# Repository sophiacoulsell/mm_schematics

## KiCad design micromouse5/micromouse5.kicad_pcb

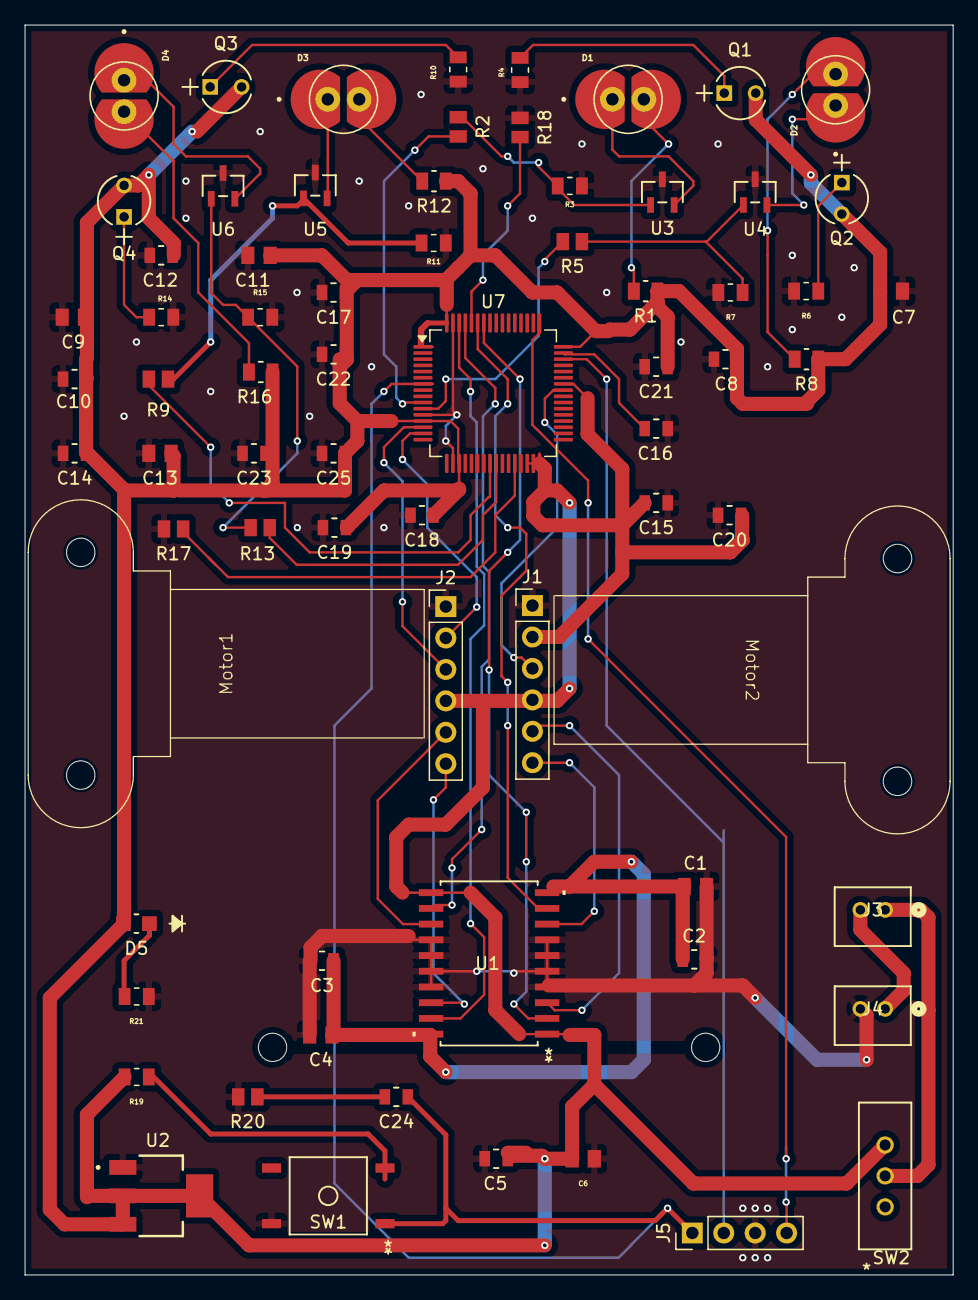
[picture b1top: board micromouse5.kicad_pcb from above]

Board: 2 copper layers, 75.0 x 101.0 mm, 71 parts (0 on the bottom side), 45 nets.

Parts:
C1, C4, C7, C9, C11, C13: 4.7 uF; CAP_GRM0805_2X1P25_MUR
C2: 10 uF; G-21_MUR(0.1)
C3: 0.1 uF; G-21_MUR(10)
C5: 10 uF; G-21_MUR(10)
C6: 22 uF; CAPC2012X140N
C8, C10, C12, C14: 0.1uF; G-21_MUR(0.1)
C15, C16: 2.2 uF; G-21_MUR
C17, C18, C19, C20, C21, C22, C23, C24: 0.1 uF; G-21_MUR(0.1)
C25: 1 uF; G-21_MUR (1uF)
D1, D2, D3, D4: IR Emitter; DIO_SFH_4545 (IR- Emitter)
D5: LED; LED_LTST-C170GKT_LTO
J1, J2: Conn_01x06_Pin; PinHeader_1x06_P2.54mm_Vertical
J3: JST 2; CONN2_B2B-PH-K-S_JST
J4: JST 1; CONN2_B2B-PH-K-S_JST
J5: Conn_01x04_Pin; PinHeader_1x04_P2.54mm_Vertical
Motor1, Motor2: Pololu_Motor
Q1, Q2, Q3, Q4: IR Receiver; NoneP157X157-2_LTO (IR- Receiver)
R1, R8, R12, R16: 51 Ohm; BO_CR0805(51 ohm)
R2, R5, R9, R13, R20: 100 Ohm; STA_RNCP0805_STP(100 ohm)
R3, R7, R11, R15: 47 kOhm; RESC2012X60N (47kΩ)
R4, R6, R10, R14: 1.8kOhm; RESC2012X60N (1.8kΩ)
R17, R18: 10 kOhm; STA_RNCP0805_STP
R19: 47k Ohm; RESC2012X60N (47kΩ)
R21: 300 Ohm; RESC2012X60N
SW1: Button; SW4_FSM4JSMA_TEC
SW2: EG1218; SW_1218_EWI
U1: HBridge; SO-20_STM
U2: Voltage Regulator; SOT230P700X185-4N
U3, U4, U5, U6: MOSFET; SOT-23_3L_ONS (mosfet)
U7: STM32F205RGTx; LQFP-64_10x10mm_P0.5mm

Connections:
3V3: C5.1, C6.1, C7.2, C8.2, C9.2, C10.2, C11.2, C12.2, C13.2, C14.2, C15.2, C17.2, C18.2, C19.2, C20.2, C21.2, C22.2, C23.1, C25.1, D5.2 (A), J1.2, J1.4, J2.4, Q1.2, Q2.2, Q3.2, Q4.2, R1.2, R8.2, R12.2, R16.2, R19.1, SW2.1, U1.1 (ENABLE_1), U1.11 (ENABLE_2), U2.2 (OUTPUT), U2.3 (INPUT), U2.4 (VOUT), U7.1 (VBAT), U7.13 (VDDA), U7.19 (VDD), U7.30 (PB11), U7.31 (VCAP_1), U7.32 (VDD), U7.42 (PA9), U7.48 (VDD), U7.64 (VDD)
GND: C1.1, C2.2, C3.1, C4.2, C5.2, C6.2, C7.1, C8.1, C9.1, C10.1, C11.1, C12.1, C13.1, C14.1, C15.1, C16.1, C17.1, C18.1, C19.1, C20.1, C21.1, C22.1, C23.2, C25.2, J1.1, J2.1, J4.2, J5.3, R3.1, R4.1, R6.1, R7.1, R10.1, R11.1, R14.1, R15.1, R17.2, R18.1, R20.2, R21.2, SW1.4, U1.4 (GND), U1.5 (GND), U1.6 (GND), U1.7 (GND), U1.14 (GND), U1.15 (GND), U1.16 (GND), U1.17 (GND), U2.1 (GND), U3.3, U4.3, U5.3, U6.3, U7.12 (VSSA), U7.18 (VSS), U7.63 (VSS)
ML1: J1.6, U1.8 (OUTPUT_2)
ML2: J1.5, U1.3 (OUTPUT_1)
MR1: J2.6, U1.18 (OUTPUT_4)
MR2: J2.5, U1.13 (OUTPUT_3)
NRST: C24.1, J5.1, SW1.1, U7.7 (NRST)
unnamed: C24.2, R20.1
unnamed: D1.A, R1.1
unnamed: D1.C, U3.2
unnamed: D2.A, R8.1
unnamed: D2.C, U4.2
unnamed: D3.A, R12.1
unnamed: D3.C, U5.2
unnamed: D4.A, R16.1
unnamed: D4.C, U6.2
unnamed: D5.1 (K), R21.1
unnamed: J3.1, SW2.2
unnamed: J3.2, J4.1
unnamed: Q1.1, R4.2
unnamed: Q2.1, R6.2
unnamed: Q3.1, R10.2
unnamed: Q4.1, R14.2
unnamed: R2.2, R3.2, U3.1
unnamed: R5.2, R7.2, U4.1
unnamed: R9.2, R11.2, U5.1
unnamed: R13.2, R15.2, U6.1
unnamed: R19.2, SW1.2
unnamed: R18.2, U7.60 (BOOT0)
unnamed: R17.1, U7.28 (PB2)
unnamed: C16.2, U7.47 (VCAP_2)
PA0: J2.3, U7.14 (PA0)
PA1: J2.2, U7.15 (PA1)
PA8: J1.3, U7.41 (PA8)
PB6: U1.2 (INPUT_1), U7.58 (PB6)
PB7: U1.9 (INPUT_2), U7.59 (PB7)
PB8: U1.12 (INPUT_3), U7.61 (PB8)
PB9: U1.19 (INPUT_4), U7.62 (PB9)
PC2: R2.1, U7.10 (PC2)
PC3: R5.1, U7.11 (PC3)
PC4: R9.1, U7.24 (PC4)
PC5: R13.1, U7.25 (PC5)
SWCLK: J5.4, U7.49 (PA14)
SWDIO: J5.2, U7.46 (PA13)
VCC: C1.2, C2.1, C3.2, C4.1, U1.10 (VS), U1.20 (VSS)

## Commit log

2025-02-21 added initial project
2025-02-21 added h-bridge
2025-02-21 added voltage regulator
2025-02-26 Schematic MM
    Assignment 5
2025-02-26 Trying to commit footprints
2025-02-27 Made shared footprints library found under /footprints/micromouse5.pretty
2025-02-28 Footprints added to folder
2025-03-01 updated footprint associations
2025-03-01 More associations
2025-03-01 Another association
2025-03-01 missing resistor associations
2025-03-01 51 ohm fix
2025-03-01 fix naming
2025-03-03 Increased size of schematic and created groups/text labels
2025-03-03 Microcontroller addition
2025-03-03 Final cleanup
2025-03-05 Updated Labels
2025-03-05 Added light
2025-03-06 Fixed pin association errors and mapped microcontroller pins to actual pins on our components.
2025-03-07 Finished Schematic
2025-03-07 Update fp-info-cache
2025-03-08 PCB start
2025-03-09 pcb work
2025-03-27 more vias
2025-03-27 More vias and microcontroller connections
2025-03-28 finished connections
2025-04-07 Revised changes
2025-04-08 fixed DRC errors
2025-04-08 ensure commit contains correct pcb
